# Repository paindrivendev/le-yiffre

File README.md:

# Le Yiffre

Le Yiffre is a modified hotswap Le Chiffre pcb as an experimental design with different thumb clusters.Thanks to tominabox1 for creating [Le Chiffre Keyboard](https://github.com/tominabox1/Le-Chiffre-Keyboard) and making it open source.

## Description

PCB, 3d case and switch plates tested and works fine. Building one is your own
risk.

## QMK Configuration

Works with le chiffre qmk config.

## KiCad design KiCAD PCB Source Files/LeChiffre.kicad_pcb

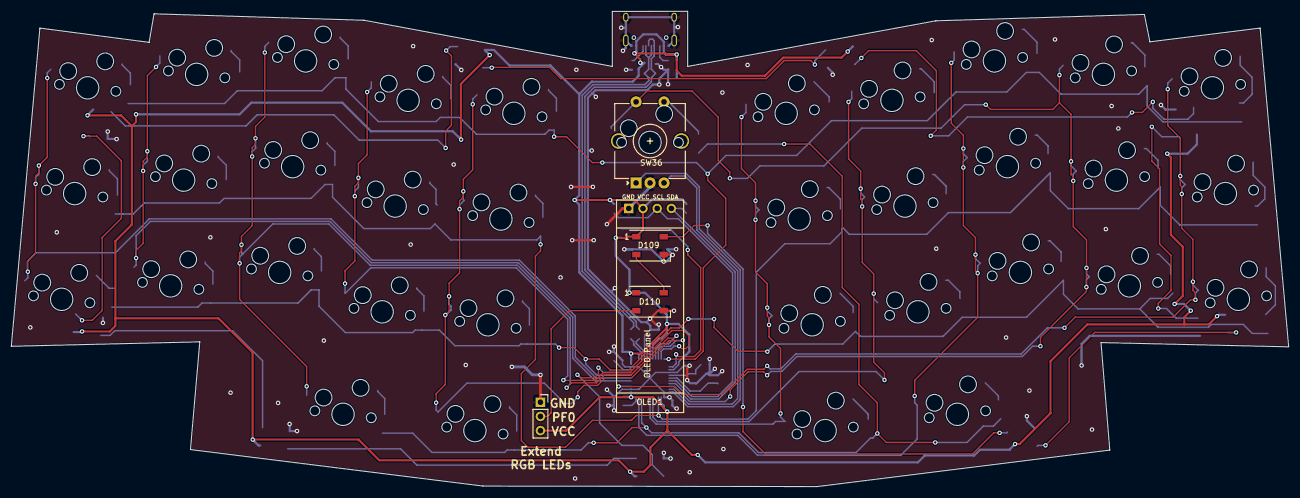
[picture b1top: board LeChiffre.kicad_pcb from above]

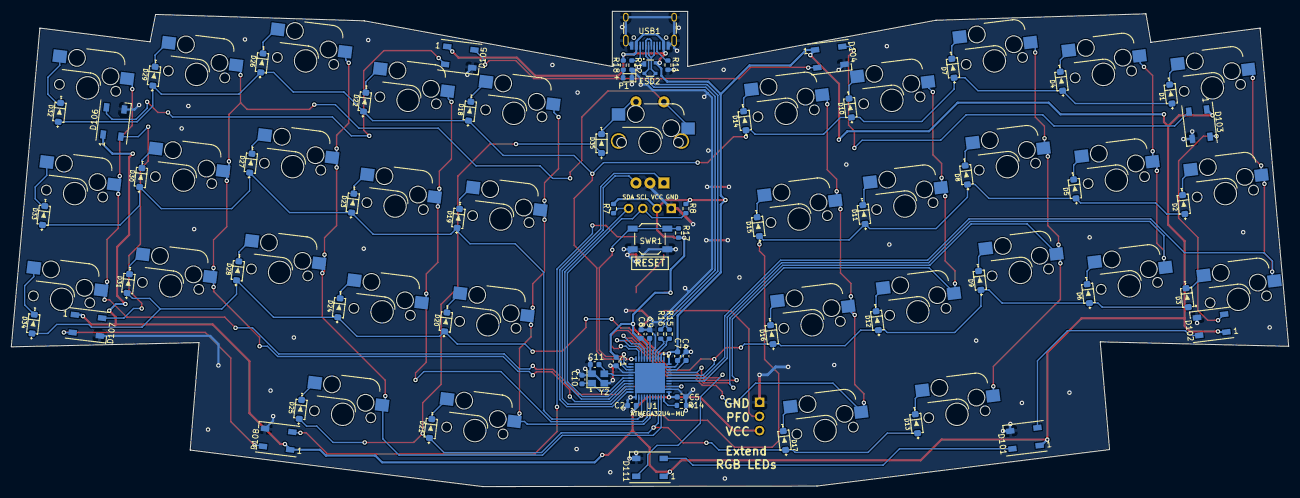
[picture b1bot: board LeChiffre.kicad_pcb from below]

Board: 2 copper layers, 228.4 x 85.0 mm, 108 parts (103 on the bottom side), 80 nets.

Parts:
C1, C2, C4, C5, C7: 100nf; C_0603_1608Metric
C8: 4.7uf; C_0603_1608Metric
C9: 1uf; C_0603_1608Metric
C10, C11: 22pf; C_0603_1608Metric
D1, D2, D3, D4, D5, D6, D7, D8, D9, D10, D11, D12, D13, D14, D15, D16, D17, D18, D19, D20, D21, D22, D23, D24, D25, D26, D27, D28, D29, D30, D31, D32, D33, D34, D35: 1N4148; D_SOD-123
D101, D102, D103, D104, D105, D106, D107, D108, D109, D110, D111: WS2812B; LED_WS2812B_PLCC4_5.0x5.0mm_P3.2mm
ESD2: PRTR5V0U2X
J1: Conn_01x03_Female; PinSocket_1x03_P2.54mm_Vertical
OLED1: Screw_Terminal_01x04; SSD1306-0.91-OLED-4pin-128x32
P1: LED; LED_0603_1608Metric
R7, R8: 4.7k; R_0603_1608Metric
R11, R12: 5.1K; R_0603_1608Metric
R14, R17: 10k; R_0603_1608Metric
R15, R16: 22; R_0603_1608Metric
R18: 470; R_0603_1608Metric
SW2, SW3, SW4, SW5, SW6, SW7, SW8, SW9, SW10, SW11, SW12, SW13, SW14, SW15, SW16, SW17, SW18, SW19, SW20, SW21, SW22, SW23, SW24, SW25, SW26, SW27, SW28, SW29, SW30, SW31, SW32, SW33, SW34, SW35, SW37: SW_Push; SW_Hotswap_Kailh_1.00u_rev
SW36: Rotary_Encoder_Switch; RotaryEncoder_Alps_EC12E-Switch_Vertical_H20mm_CircularMoun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
SWR1: SW_Push; K2-1187SQ-A4SW-06
U1: ATMEGA32U4-MU; ATMEGA32U4-MURr
USB1: USB_C_Receptacle_USB2.0; USB_C_Receptacle_HRO_TYPE-C-31-M-12
Y2: Crystal_GND23; Crystal_SMD_3225-4Pin_3.2x2.5mm

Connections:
+5V: C1.1, C2.1, C5.1, C7.1, C8.1, D101.1 (VDD), D102.1 (VDD), D103.1 (VDD), D104.1 (VDD), D105.1 (VDD), D106.1 (VDD), D107.1 (VDD), D108.1 (VDD), D109.1 (VDD), D110.1 (VDD), D111.1 (VDD), ESD2.4 (VCC), J1.3 (Pin_1), OLED1.2, R7.2, R8.2, R17.1, R18.2, U1.2 (UVCC), U1.7 (VBUS), U1.14 (VCC_1), U1.24 (AVCC_1), U1.34 (VCC_2), U1.44 (AVCC_2), USB1.A4 (VBUS), USB1.A9 (VBUS), USB1.B4 (VBUS), USB1.B9 (VBUS)
DN: ESD2.3 (I/O2), R15.2, USB1.A7 (D-), USB1.B7 (D-)
DP: ESD2.2 (I/O1), R16.2, USB1.A6 (D+), USB1.B6 (D+)
D_N: R15.1, U1.3 (D-)
D_P: R16.1, U1.4 (D+)
EncA: SW36.A, U1.22 ((XCK1/~CTS)_PD5)
EncB: SW36.B, U1.21 ((TXD1/INT3)_PD3)
GND: C1.2, C2.2, C4.1, C5.2, C7.2, C8.2, C9.1, C10.2, C11.2, D101.3 (VSS), D102.3 (VSS), D103.3 (VSS), D104.3 (VSS), D105.3 (VSS), D106.3 (VSS), D107.3 (VSS), D108.3 (VSS), D109.3 (VSS), D110.3 (VSS), D111.3 (VSS), ESD2.1 (GND), J1.1 (Pin_3), OLED1.1, P1.1 (K), R11.1, R12.1, R14.2, SW36.C, SWR1.1, U1.5 (UGND), U1.15 (GND_1), U1.23 (GND_2), U1.35 (GND_3), U1.43 (GND_4), U1.45 (EP), USB1.A1 (GND), USB1.A12 (GND), USB1.B1 (GND), USB1.B12 (GND), USB1.S1 (SHIELD), Y2.2, Y2.4
LED: D111.4 (DIN), U1.41 (PF0_(ADC0))
unnamed: D1.1 (K), SW2.1
unnamed: D2.1 (K), SW3.1
unnamed: D3.1 (K), SW4.1
unnamed: D4.1 (K), SW5.1
unnamed: D5.1 (K), SW6.1
unnamed: D6.1 (K), SW7.1
unnamed: D7.1 (K), SW8.1
unnamed: D8.1 (K), SW9.1
unnamed: D9.1 (K), SW10.1
unnamed: D10.1 (K), SW11.1
unnamed: D11.1 (K), SW12.1
unnamed: D12.1 (K), SW13.1
unnamed: D13.1 (K), SW14.1
unnamed: D14.1 (K), SW15.1
unnamed: D15.1 (K), SW16.1
unnamed: D16.1 (K), SW17.1
unnamed: D17.1 (K), SW18.1
unnamed: D18.1 (K), SW19.1
unnamed: D19.1 (K), SW20.1
unnamed: D20.1 (K), SW21.1
unnamed: D21.1 (K), SW22.1
unnamed: D22.1 (K), SW23.1
unnamed: D23.1 (K), SW24.1
unnamed: D24.1 (K), SW25.1
unnamed: D25.1 (K), SW26.1
unnamed: D26.1 (K), SW27.1
unnamed: D27.1 (K), SW28.1
unnamed: D28.1 (K), SW29.1
unnamed: D29.1 (K), SW30.1
unnamed: D30.1 (K), SW31.1
unnamed: D31.1 (K), SW32.1
unnamed: D32.1 (K), SW33.1
unnamed: D33.1 (K), SW34.1
unnamed: D34.1 (K), SW35.1
unnamed: D35.1 (K), SW36.S1, SW37.1
unnamed: D101.4 (DIN), D111.2 (DOUT)
unnamed: D101.2 (DOUT), D102.4 (DIN)
unnamed: D102.2 (DOUT), D103.4 (DIN)
unnamed: D103.2 (DOUT), D104.4 (DIN)
unnamed: D104.2 (DOUT), D105.4 (DIN)
unnamed: D105.2 (DOUT), D106.4 (DIN)
unnamed: D106.2 (DOUT), D107.4 (DIN)
unnamed: D107.2 (DOUT), D108.4 (DIN)
unnamed: D108.2 (DOUT), D109.4 (DIN)
unnamed: D109.2 (DOUT), D110.4 (DIN)
unnamed: D110.2 (DOUT), J1.2
unnamed: P1.2 (A), R18.1
unnamed: C4.2, U1.42 (AREF)
unnamed: R14.1, U1.33 (PE2_(H~WB))
unnamed: C9.2, U1.6 (UCAP)
unnamed: R11.2, USB1.A5 (CC1)
unnamed: R12.2, USB1.B5 (CC2)
RESET: R17.2, SWR1.2, U1.13 (~RESET)
SCK: OLED1.3, R8.1, U1.18 ((OC0B/SCL/INT0)_PD0)
SDA: OLED1.4, R7.1, U1.19 ((SDA/INT1)_PD1)
XTAL1: C10.1, U1.17 (XTAL1), Y2.1
XTAL2: C11.1, U1.16 (XTAL2), Y2.3
col0: SW2.2, SW3.2, SW4.2, U1.39 (PF4_(ADC4/TCK))
col1: SW5.2, SW6.2, SW7.2, U1.38 (PF5_(ADC5/TMS))
col2: SW8.2, SW9.2, SW10.2, SW14.2, U1.8 ((SS/PCINT0)_PB0)
col3: SW11.2, SW12.2, SW13.2, U1.10 ((PDI/PCINT2/MOSI)_PB2)
col4: SW15.2, SW16.2, SW17.2, SW18.2, U1.9 ((PCINT1/SCLK)_PB1)
col5: SW19.2, SW20.2, SW21.2, SW22.2, U1.28 (PB4_(PCINT4/ADC11))
col6: SW23.2, SW24.2, SW25.2, U1.27 (PD7_(T0/OC4D/ADC10))
col7: SW26.2, SW27.2, SW28.2, SW29.2, U1.32 (PC7_(ICP3/CLK0/OC4A))
col8: SW30.2, SW31.2, SW32.2, SW36.S2, SW37.2, U1.20 ((RXD1/INT2)_PD2)
col9: SW33.2, SW34.2, SW35.2, U1.36 (PF7_(ADC7/TDI))
row0: D1.2 (A), D4.2 (A), D7.2 (A), D10.2 (A), D14.2 (A), D18.2 (A), D22.2 (A), D26.2 (A), D29.2 (A), D32.2 (A), U1.11 ((PDO/PCINT3/MISO)_PB3)
row1: D2.2 (A), D5.2 (A), D8.2 (A), D11.2 (A), D15.2 (A), D19.2 (A), D23.2 (A), D27.2 (A), D30.2 (A), D33.2 (A), U1.25 (PD4_(ICP1/ADC8))
row2: D3.2 (A), D6.2 (A), D9.2 (A), D12.2 (A), D16.2 (A), D20.2 (A), D24.2 (A), D28.2 (A), D31.2 (A), D34.2 (A), U1.40 (PF1_(ADC1))
row3: D13.2 (A), D17.2 (A), D21.2 (A), D25.2 (A), D35.2 (A), U1.31 (PC6_(OC3A/~OC4A))

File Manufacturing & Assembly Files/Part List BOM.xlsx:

Item | Qty | Reference(s) | Value | Footprint | JLCPCB Part# | Weblink | Column1
1 | 5 | C1, C2, C4, C5, C7 | 100nf | Ahsan Libs:C_0603_1608Metric | C14663 | https://lcsc.com/product-detail/Multilayer-Ceramic-Capacitor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
2 | 1 | C8 | 4.7uf | Ahsan Libs:C_0603_1608Metric | C19666 | https://www.lcsc.com/product-detail/Multilayer-Ceramic-Capac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
3 | 1 | C9 | 1uf | Ahsan Libs:C_0603_1608Metric | C15849 | https://lcsc.com/product-detail/Multilayer-Ceramic-Capacitor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
4 | 2 | C10, C11 | 22pf | Ahsan Libs:C_0603_1608Metric | C1653 | https://lcsc.com/product-detail/Multilayer-Ceramic-Capacitor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
5 | 34 | D1, D2, D3, D4, D5, D6, D7, D8, D9, D10, D11, D12, D13, D14, D15, D16, D17, D18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 | 1N4148 | Ahsan Libs:D_SOD-123 | C81598 | https://lcsc.com/product-detail/Switching-Diode_ST-Semtech-1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
6 | 11 | D101, D102, D103, D104, D105, D106, D107, D108, D109, D110, D111 | WS2812B | LED_SMD:LED_WS2812B_PLCC4_5.0x5.0mm_P3.2mm | C2761795 | https://www.lcsc.com/product-detail/Light-Emitting-Diodes-LE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
7 | 1 | ESD2 | PRTR5V0U2X | Ahsan Libs:PRTR5V0U2X | C2827688 | https://lcsc.com/product-detail/ESD-Protection-Devices_TECH-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
8 | 1 | OLED1 | Screw_Terminal_01x04 | Ahsan Libs:SSD1306-0.91-OLED-4pin-128x32 | C5116530 | https://www.lcsc.com/product-detail/Female-Headers_ZHOURI-PM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
9 | 1 | P1 | LED | Ahsan Libs:LED_0603_1608Metric | C72041 | https://lcsc.com/product-detail/Light-Emitting-Diodes-LED_Ev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
10 | 2 | R7, R8 | 4.7k | Ahsan Libs:R_0603_1608Metric | C23162 | https://www.lcsc.com/product-detail/Chip-Resistor-Surface-Mo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
11 | 2 | R11, R12 | 5.1K | Ahsan Libs:R_0603_1608Metric | C23186 | https://lcsc.com/product-detail/Chip-Resistor-Surface-Mount_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
12 | 2 | R14, R17 | 10k | Ahsan Libs:R_0603_1608Metric | C25804 | https://lcsc.com/product-detail/Chip-Resistor-Surface-Mount_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
13 | 1 | R15 | 22 | Ahsan Libs:R_0603_1608Metric | C1203 | https://lcsc.com/product-detail/Chip-Resistor-Surface-Mount_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
14 | 1 | R16 | 22 | Ahsan Libs:R_0603_1608Metric | C1203 | https://lcsc.com/product-detail/Chip-Resistor-Surface-Mount_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
15 | 1 | R18 | 470 | Ahsan Libs:R_0603_1608Metric | C23179 | https://lcsc.com/product-detail/Chip-Resistor-Surface-Mount_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
16 | 35 | SW2, SW3, SW4, SW5, SW6, SW7, SW8, SW9, SW10, SW11, SW12, SW13, SW14, SW15, SW1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 | SW_Push | Ahsan Libs:SW_Hotswap_Kailh_1.00u_rev | C5156480 | https://lcsc.com/product-detail/Mechanical-Keyboard-Shaft_Ka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 | https://shop.keyboard.io/products/kailh-hotswap-sockets-for-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
17 | 1 | SW36 | Rotary_Encoder_Switch | Rotary_Encoder:RotaryEncoder_Alps_EC12E-Switch_Vertical_H20mm_CircularMountingH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 | C370992 | https://www.lcsc.com/product-detail/Rotary-Encoders_ALPSALPI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
18 | 1 | SWR1 | SW_Push | Ahsan Libs:K2-1187SQ-A4SW-06 | C388295 | https://lcsc.com/product-detail/Tactile-Switches_SHOU-HAN-TS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
19 | 1 | U1 | ATMEGA32U4-MU | Ahsan Libs:ATMEGA32U4-MURr | C112161 | https://lcsc.com/product-detail/ATMEL-AVR_Microchip-Tech-ATM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
20 | 1 | USB1 | USB_C_Receptacle_USB2.0 | Ahsan Libs:USB_C_Receptacle_HRO_TYPE-C-31-M-12 | C165948 | https://www.lcsc.com/product-detail/USB-Connectors_Korean-Hr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
21 | 1 | Y2 | Crystal_GND23 | Ahsan Libs:Crystal_SMD_3225-4Pin_3.2x2.5mm | C13738 | https://lcsc.com/product-detail/Crystals_Yangxing-Tech-X3225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
